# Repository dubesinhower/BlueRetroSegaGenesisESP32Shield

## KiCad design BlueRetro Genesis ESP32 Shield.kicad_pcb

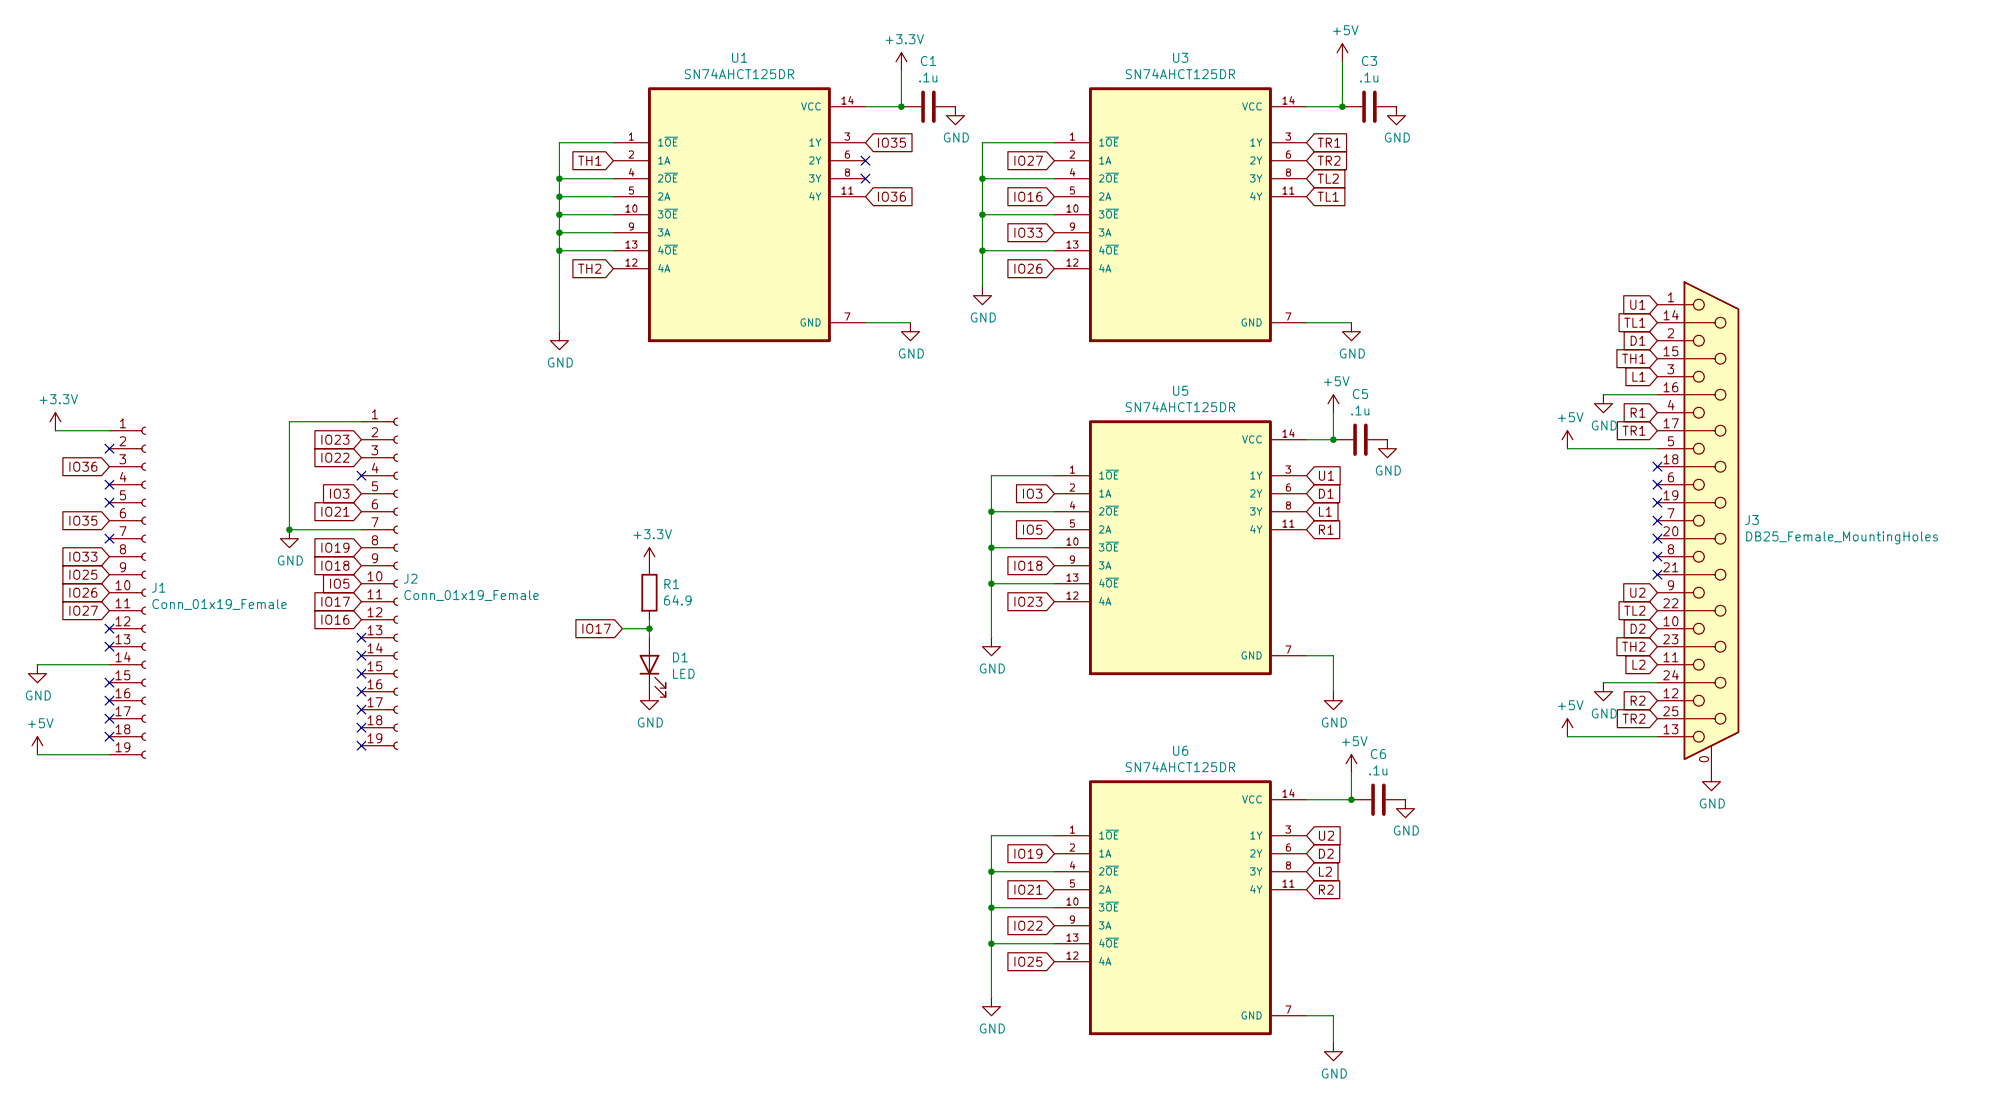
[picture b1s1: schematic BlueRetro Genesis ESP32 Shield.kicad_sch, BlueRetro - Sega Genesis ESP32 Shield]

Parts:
C1, C3, C5, C6: .1u; C_0603_1608Metric_Pad1.08x0.95mm_HandSolder
D1: LED; LED_0603_1608Metric
J1, J2: Conn_01x19_Female; PinSocket_1x19_P2.54mm_Vertical
J3: DB25_Female_MountingHoles; DSUB-25_Female_Horizontal_P2.77x2.84mm_EdgePinOffset7.70mm_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
R1: 64.9; R_0603_1608Metric
U1, U3, U5, U6: SN74AHCT125DR; SOIC127P600X175-14N

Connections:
+3V3: C1.2, J1.1, R1.1, U1.14 (VCC)
+5V: C3.2, C5.2, C6.2, J1.19, J3.5, J3.13, U3.14 (VCC), U5.14 (VCC), U6.14 (VCC)
D1: J3.2, U5.6 (2Y)
D2: J3.10, U6.6 (2Y)
GND: C1.1, C3.1, C5.1, C6.1, D1.1 (K), J1.14, J2.1, J2.7, J3.0 (PAD), J3.16, J3.24, U1.1 (1~OE), U1.4 (2~OE), U1.5 (2A), U1.7 (GND), U1.9 (3A), U1.10 (3~OE), U1.13 (4~OE), U3.1 (1~OE), U3.4 (2~OE), U3.7 (GND), U3.10 (3~OE), U3.13 (4~OE), U5.1 (1~OE), U5.4 (2~OE), U5.7 (GND), U5.10 (3~OE), U5.13 (4~OE), U6.1 (1~OE), U6.4 (2~OE), U6.7 (GND), U6.10 (3~OE), U6.13 (4~OE)
IO3: J2.5, U5.2 (1A)
IO5: J2.10, U5.5 (2A)
IO16: J2.12, U3.5 (2A)
IO17: D1.2 (A), J2.11, R1.2
IO18: J2.9, U5.9 (3A)
IO19: J2.8, U6.2 (1A)
IO21: J2.6, U6.5 (2A)
IO22: J2.3, U6.9 (3A)
IO23: J2.2, U5.12 (4A)
IO25: J1.9, U6.12 (4A)
IO26: J1.10, U3.12 (4A)
IO27: J1.11, U3.2 (1A)
IO33: J1.8, U3.9 (3A)
IO35: J1.6, U1.3 (1Y)
IO36: J1.3, U1.11 (4Y)
L1: J3.3, U5.8 (3Y)
L2: J3.11, U6.8 (3Y)
R1: J3.4, U5.11 (4Y)
R2: J3.12, U6.11 (4Y)
TH1: J3.15, U1.2 (1A)
TH2: J3.23, U1.12 (4A)
TL1: J3.14, U3.11 (4Y)
TL2: J3.22, U3.8 (3Y)
TR1: J3.17, U3.3 (1Y)
TR2: J3.25, U3.6 (2Y)
U1: J3.1, U5.3 (1Y)
U2: J3.9, U6.3 (1Y)

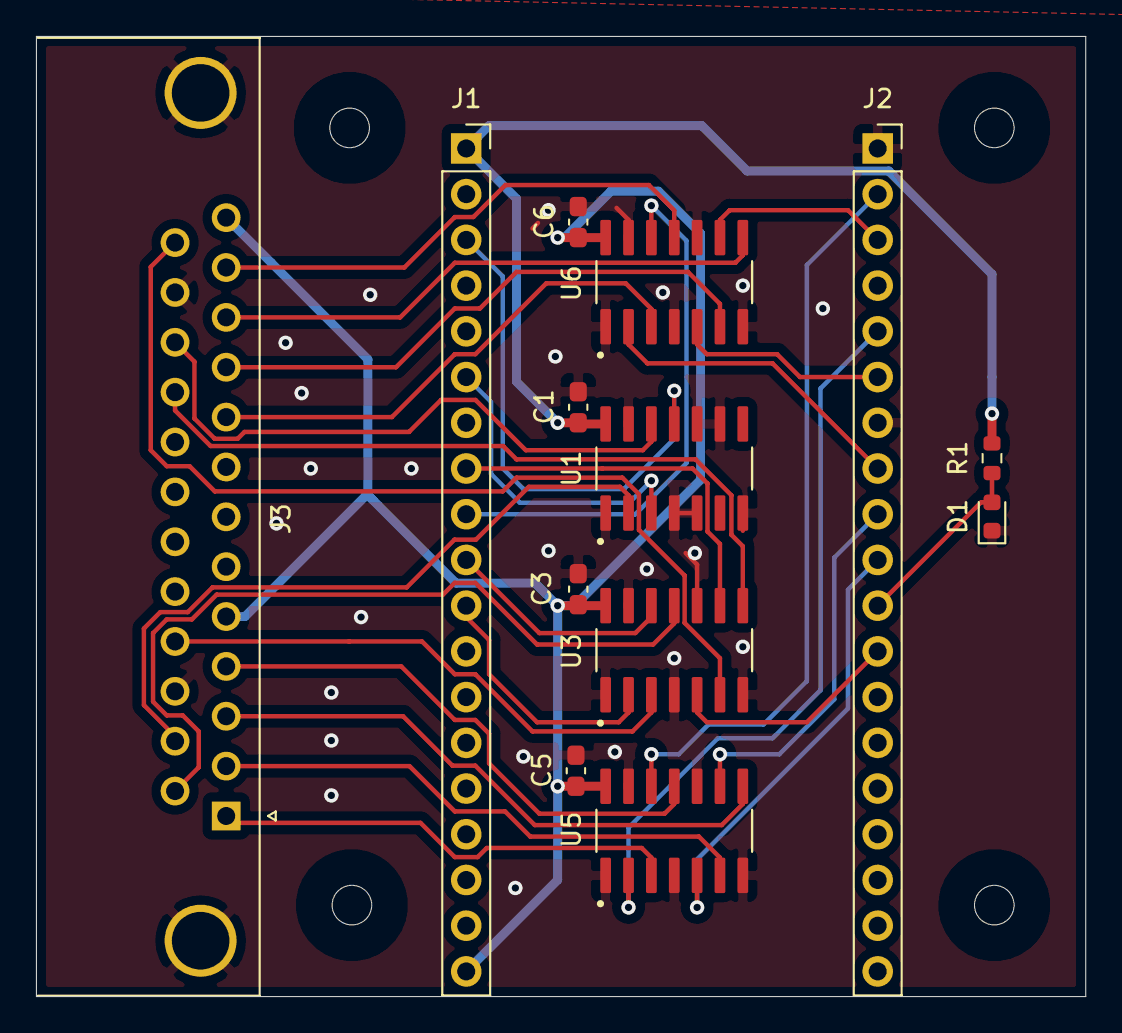
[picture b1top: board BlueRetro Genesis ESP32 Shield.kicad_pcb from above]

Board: 2 copper layers, 58.3 x 53.3 mm, 13 parts (0 on the bottom side), 32 nets.

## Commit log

2021-12-26 initial-commit
    Initial commit, first version of BlueRetro Genesis shield

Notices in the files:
BlueRetro Genesis ESP32 Shield.kicad_sch:
© 2021 Dubesinhower, licensed under CC-BY-4.0
